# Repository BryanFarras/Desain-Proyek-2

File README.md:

# Autonomous Evacuation Rover (AER)

Autonomous Evacuation Rover (AER) is an integrated mobile robotics platform developed for autonomous exploration, mapping, hazard detection, and evacuation assistance in unknown or hazardous indoor environments. The system combines ROS 2-based autonomous navigation (SLAM and Nav2), real-time deep learning obstacle detection (YOLOv8), an embedded dual-motor controller (ESP32 and TB6612FNG), and a real-time web monitoring dashboard designed for both onboard touchscreen kiosks and remote operator telemetry.

---

## Table of Contents

- [System Architecture](#system-architecture)
- [Key Features](#key-features)
- [Repository Structure](#repository-structure)
- [Hardware Specifications](#hardware-specifications)
- [Software Stack and Prerequisites](#software-stack-and-prerequisites)
- [Installation and Environment Setup](#installation-and-environment-setup)
  - [Automated Installation](#automated-installation)
  - [Manual Installation](#manual-installation)
- [Subsystem Configuration and Execution](#subsystem-configuration-and-execution)
  - [1. Web Monitoring System](#1-web-monitoring-system)
  - [2. Computer Vision and Obstacle Detection](#2-computer-vision-and-obstacle-detection)
  - [3. ROS 2 Simulation, SLAM, and Navigation](#3-ros-2-simulation-slam-and-navigation)
  - [4. ESP32 Motor Controller Firmware](#4-esp32-motor-controller-firmware)
- [Communication and Control Protocols](#communication-and-control-protocols)
  - [ESP32 UART Serial Protocol](#esp32-uart-serial-protocol)
  - [Web Monitoring Endpoints](#web-monitoring-endpoints)
  - [ROS 2 Topic Architecture](#ros-2-topic-architecture)
- [Hardware Design and PCB](#hardware-design-and-pcb)
- [Troubleshooting](#troubleshooting)
- [License and Project Information](#license-and-project-information)

---

## System Architecture

The robot utilizes a distributed computing model comprising a primary Single Board Computer (Raspberry Pi 4B) and an auxiliary Microcontroller Unit (ESP32 DOIT DevKit V1), linked over high-speed USB-UART serial communication:

```
+-----------------------------------------------------------------------+
|                    Raspberry Pi 4B (Host Computer)                    |
|                                                                       |
|  +---------------------------+       +-----------------------------+  |
|  |     ROS 2 Jazzy Stack     |       |   Computer Vision Pipeline  |  |
|  |  - SLAM Toolbox (Mapping) |       |  - YOLOv8 Obstacle Model    |  |
|  |  - Beluga AMCL (Localize) |       |  - Picamera2 / OpenCV       |  |
|  |  - Nav2 (Path Planning)   |       |  - Real-time Bounding Boxes |  |
|  +-------------+-------------+       +--------------+--------------+  |
|                |                                    |                 |
|                +------------------+-----------------+                 |
|                                   |                                   |
|                      +------------v------------+                      |
|                      |  Flask Monitoring Server|                      |
|                      |  - Telemetry Dashboard  |                      |
|                      |  - Live MJPEG Stream    |                      |
|                      |  - Mission Mode Control |                      |
|                      |  - Emergency Stop / HITL|                      |
|                      +------------+------------+                      |
|                                   |                                   |
|                         [Serial Bridge: 115200]                       |
+-----------------------------------|-----------------------------------+
                                    | USB-UART
+-----------------------------------v-----------------------------------+
|                        ESP32 DOIT DevKit V1                           |
|                                                                       |
|  - PWM Motor Generation (20 kHz, 8-bit resolution)                    |
|  - Bidirectional Movement Logic (Differential Drive)                 |
|  - TB6612FNG Dual H-Bridge Driver Interface                          |
|  - Safety Watchdog and Standby Management                            |
+-----------------------------------+-----------------------------------+
                                    |
                            +-------v-------+
                            | DC Gear Motors|
                            +---------------+
```

---

## Key Features

- **Autonomous Navigation and SLAM**: Full ROS 2 navigation integration utilizing `slam_toolbox` for 2D LiDAR mapping, `beluga_amcl` for probabilistic particle-filter localization, and `nav2` for global/local path planning and dynamic costmaps.
- **Deep Learning Obstacle Detection**: Onboard real-time inference using YOLOv8 Nano models tailored for low-power edge compute, supporting Picamera2 on Raspberry Pi OS and OpenCV fallback on desktop workstations.
- **Dedicated Low-Level Motor Control**: ESP32 firmware running high-frequency 20 kHz PWM for quiet and responsive motor actuation, eliminating timing jitter and isolating motor power noise from the primary processor.
- **Comprehensive Web Monitoring Interface**: Flask-based web dashboard offering live teleoperation, real-time telemetry gauges (odometry, yaw, speed, battery, CPU/RAM stats), MJPEG video feed, dynamic whitelisted system diagnostics, and hardware emergency stop triggers.
- **Touchscreen Kiosk Capability**: Optimized layout for 3.2-inch to 7-inch Raspberry Pi LCDs with support for full-screen Chromium kiosk autostart and background systemd service operation.
- **Custom Hardware Infrastructure**: Dedicated custom PCB designs (Gerber files provided) for clean power delivery, level shifting, motor driver routing, and sensor connectivity.

---

## Repository Structure

```
.
|-- Computer Vision/              # AI training pipelines and camera inference
|   |-- cv_ws/                    # Computer vision workspace resources
|   |-- requirements.txt          # CV specific Python dependencies
|   |-- run_picam_rover.py        # Real-time YOLOv8 camera inference runner
|   |-- standalone_cv.py          # Standalone video test script
|   |-- train_rover.py            # Model training and export (ONNX, TFLite, NCNN)
|   `-- README_TRAINING_PICAM.md  # Detailed training and deployment documentation
|-- Dataset CV/                   # Training and validation datasets for obstacle detection
|-- Docs/                         # Project documentation and setup guides
|   `-- LANGKAH_PEMBUATAN_MODEL_CV.md # Indonesian guide for CV model creation
|-- Monitoring System/            # Legacy telemetry and monitoring code
|-- New Monitoring System/        # Production Flask monitoring and control dashboard
|   |-- aer-dashboard.service     # Systemd unit file for autostart
|   |-- camera_stream.py          # Multi-backend camera streamer (Picamera2/OpenCV)
|   |-- main.py                   # Primary Flask application server and state machine
|   |-- requirements.txt          # Dashboard Python dependencies
|   |-- ros2_node.py              # ROS 2 rclpy node bridge for telemetry
|   |-- serial_bridge.py          # UART communication driver for ESP32
|   |-- setup.sh                  # Dashboard quick-setup script
|   |-- static/                   # CSS stylesheets, JavaScript files, and assets
|   |-- templates/                # Jinja2 HTML dashboard templates
|   `-- README.md                 # Detailed dashboard documentation
|-- PCB/                          # Hardware design files and manufacturing archives
|   |-- Gerber New/               # Updated PCB Gerber fabrication files
|   `-- Rover Gerber/             # Primary chassis PCB Gerber package
|-- RoverESP/                     # ESP32 motor controller firmware (PlatformIO)
|   |-- include/                  # C++ header files
|   |-- lib/                      # PlatformIO modular libraries
|   |-- platformio.ini            # PlatformIO board and build configuration
|   `-- src/
|       |-- TB6612FNG.cpp         # TB6612FNG motor driver implementation
|       `-- main.cpp              # Serial listener and motor actuation loop
|-- Rover_Sim/                    # ROS 2 simulation and autonomy workspace
|   |-- maze_map_save.pgm         # Saved occupancy grid map
|   |-- maze_map_save.yaml        # Map metadata configuration
|   `-- src/
|       |-- AREbot_description/   # Robot URDF, Xacro, meshes, and launch files
|       |-- beluga/               # Beluga localization library
|       |-- beluga_amcl/          # Beluga AMCL 2D localization ROS 2 package
|       |-- beluga_ros/           # Beluga ROS 2 integration wrappers
|       `-- ldlidar_stl_ros2/     # LDLiDAR STL-27L driver package
|-- INSTALL_DEPENDENCIES.md       # Multi-platform dependency installation guide
|-- install_all_dependencies.ps1  # Windows PowerShell automated installer
|-- install_all_dependencies.sh   # Linux/Raspberry Pi automated installer
|-- install_ros_dependencies.sh   # Ubuntu 24.04 ROS 2 Jazzy automated installer
|-- requirements.txt              # Root unified Python dependencies
`-- setup_python_env.sh           # Virtual environment configuration script
```

---

## Hardware Specifications

| Component | Model / Specification | Purpose |
| :--- | :--- | :--- |
| Single Board Computer | Raspberry Pi 4 Model B (4GB / 8GB) | High-level compute: ROS 2, SLAM, CV, Web Server |
| Microcontroller | ESP32 DOIT DevKit V1 (30-pin) | Low-level motor control, PWM generation, safety brake |
| Motor Driver | Toshiba TB6612FNG Dual H-Bridge | Drives left and right DC drive motors |
| Drive Motors | DC Gear Motors with Encoders | Differential drive locomotive base |
| Range Sensor | 2D LiDAR (LDLiDAR STL-27L / LD19) | Environment 360-degree range scanning for SLAM |
| Vision Sensor | Raspberry Pi Camera Module 2/3 or USB Cam | Video stream capture and YOLOv8 object detection |
| Display | 3.2-inch to 7-inch LCD Display | Onboard dashboard for local telemetry and status |
| Power Supply | Li-Ion 3S / 2S Pack + Buck Regulators | Independent 5V logic and 7.4V-12V motor supply rails |
| Custom PCB | 2-layer FR4 Custom Board | Power distribution, MCU mounting, and header breakouts |

---

## Software Stack and Prerequisites

- **Operating System**: Ubuntu 24.04 LTS (Noble Numbat) recommended for ROS 2 Jazzy; Raspberry Pi OS 64-bit (Debian Bookworm) supported for the physical robot deployment.
- **Robotics Middleware**: ROS 2 Jazzy Jalisco (or ROS 2 Humble Hawksbill on Ubuntu 22.04).
- **Python Runtime**: Python 3.10 or higher.
- **Embedded Toolchain**: PlatformIO Core (`pio`) or PlatformIO IDE in VS Code.
- **Core Python Packages**:
  - `flask >= 3.0.0`
  - `psutil >= 5.9.0`
  - `pyserial >= 3.5`
  - `opencv-python >= 4.8.0`
  - `numpy >= 1.24.0`
  - `ultralytics >= 8.0.0`
  - `torch`, `torchvision`
  - `transforms3d >= 0.4.0`
  - `websockets >= 12.0`

---

## Installation and Environment Setup

### Automated Installation

#### Linux and Raspberry Pi OS (One-Line Execution)

For standard application dependencies (Flask, PySerial, OpenCV, YOLO, system libraries):

```bash
chmod +x install_all_dependencies.sh && ./install_all_dependencies.sh
```

For a complete ROS 2 Jazzy installation with Nav2, Gazebo, and simulation dependencies on Ubuntu 24.04 LTS:

```bash
sudo bash install_ros_dependencies.sh
```

#### Windows (PowerShell)

Open PowerShell as Administrator in the root repository directory:

```powershell
Set-ExecutionPolicy -Scope Process -ExecutionPolicy Bypass
.\install_all_dependencies.ps1
```

---

### Manual Installation

#### 1. System Packages (Linux)

```bash
sudo apt-get update && sudo apt-get install -y \
    python3 python3-pip python3-venv python3-dev \
    build-essential libgl1-mesa-glx libglib2.0-0 \
    libgstreamer1.0-0 v4l-utils
```

If deploying on Raspberry Pi with the official camera:

```bash
sudo apt-get install -y python3-picamera2
```

#### 2. Python Virtual Environment

Create a virtual environment with `--system-site-packages` so ROS 2 (`rclpy`) and `picamera2` system bindings remain accessible:

```bash
python3 -m venv --system-site-packages .venv
source .venv/bin/activate
pip install --upgrade pip
pip install -r requirements.txt
```

#### 3. Serial Port Permissions (Linux)

Grant your user access to USB serial devices (`/dev/ttyUSB0` or `/dev/ttyACM0`):

```bash
sudo usermod -aG dialout $USER
```

Log out and back in for this change to take effect.

---

## Subsystem Configuration and Execution

### 1. Web Monitoring System

The monitoring system runs a Flask server that bridges ROS 2 telemetry, camera video, and direct ESP32 serial communication.

```bash
# Activate environment
source .venv/bin/activate

# Launch the monitoring server
cd "New Monitoring System"
python main.py
```

The interface will be accessible in your browser at:
`http://localhost:5000` or `http://<ROBOT_IP>:5000`

#### Running as a Background System Service (Linux)

To enable the dashboard to start automatically on system boot:

```bash
sudo cp "New Monitoring System/aer-dashboard.service" /etc/systemd/system/
sudo systemctl daemon-reload
sudo systemctl enable aer-dashboard.service
sudo systemctl start aer-dashboard.service
```

#### Kiosk Mode Configuration (Raspberry Pi Display)

To launch the dashboard full-screen in Chromium on desktop login, create an autostart entry:

```bash
mkdir -p ~/.config/autostart
cat << 'EOF' > ~/.config/autostart/aer-dashboard.desktop
[Desktop Entry]
Type=Application
Name=AER Dashboard
Exec=chromium-browser --kiosk --app=http://localhost:5000 --start-fullscreen
EOF
```

---

### 2. Computer Vision and Obstacle Detection

#### Real-Time Camera Inference

Run the detection pipeline using either a connected Raspberry Pi Camera or standard USB/OpenCV webcam:

```bash
cd "Computer Vision"

# Using OpenCV / USB Webcam:
python run_picam_rover.py --cam opencv --cam-id 0

# Using Raspberry Pi Camera Module:
python run_picam_rover.py --cam picam --conf 0.45
```

#### Model Training and Export

To train a new YOLOv8 obstacle detection model on your custom dataset:

```bash
cd "Computer Vision"
python train_rover.py --epochs 50 --imgsz 416 --batch 16 --model yolov8n.pt
```

After training, the best model weights will be saved to `runs/rover_train/rover_obstacle_model/weights/best.pt` and automatically exported to ONNX and TFLite formats for optimized execution on low-power devices.

---

### 3. ROS 2 Simulation, SLAM, and Navigation

#### Building the Simulation Workspace

```bash
source /opt/ros/jazzy/setup.bash
cd Rover_Sim
colcon build --symlink-install
source install/setup.bash
```

#### Launching Gazebo Simulation

Launch the AREbot robot model within the Gazebo simulation environment:

```bash
ros2 launch AREbot_description gazebo.launch.py
```

#### Running 2D SLAM Mapping

In a separate terminal:

```bash
source Rover_Sim/install/setup.bash
ros2 launch AREbot_description online_async_launch.py
```

#### Running Beluga AMCL Localization

To localize the robot within a pre-mapped environment:

```bash
source Rover_Sim/install/setup.bash
ros2 launch AREbot_description beluga_localizaton_amcl.launch.py
```

#### Launching Nav2 Autonomous Navigation

```bash
source Rover_Sim/install/setup.bash
ros2 launch AREbot_description nav2_script.launch.py
```

---

### 4. ESP32 Motor Controller Firmware

The firmware in `RoverESP` handles motor actuation and receives direction commands from the Raspberry Pi over UART.

#### Building and Uploading with PlatformIO

1. Connect the ESP32 to your workstation via USB.
2. Navigate to the `RoverESP` directory:
   ```bash
   cd RoverESP
   ```
3. Compile the firmware:
   ```bash
   pio run
   ```
4. Upload the binary to the ESP32:
   ```bash
   pio run --target upload
   ```
5. Open the serial monitor to verify operation:
   ```bash
   pio device monitor --baud 115200
   ```

---

## Communication and Control Protocols

### ESP32 UART Serial Protocol

The ESP32 listens on UART (115200 baud, 8N1) for single-character ASCII control commands:

| Command Character | Action | Description |
| :---: | :--- | :--- |
| `w` | Forward | Both motors rotate forward at `currentSpeed` |
| `s` | Backward | Both motors rotate backward at `currentSpeed` |
| `a` | Turn Left | Steer left (Right motor forward, Left motor reduced) |
| `d` | Turn Right | Steer right (Left motor forward, Right motor reduced) |
| `q` | Spin Left | Counter-clockwise in-place rotation |
| `e` | Spin Right | Clockwise in-place rotation |
| ` ` (Space) | Coast Stop | Disables motor PWM, allowing free rolling |
| `b` | Short Brake | Actuates active brake on both H-bridges |
| `+` | Speed Increment | Increases default PWM speed by +20 (Max 255) |
| `-` | Speed Decrement | Decreases default PWM speed by -20 (Min 0) |
| `t` | Automated Demo | Runs pre-programmed motion self-test |
| `h` | Help Menu | Prints serial command help interface |

---

### Web Monitoring Endpoints

| Endpoint | HTTP Method | Function |
| :--- | :---: | :--- |
| `/` | GET | Serves the primary monitoring web dashboard |
| `/video_feed` | GET | Streams live MJPEG video with overlay graphics |
| `/status` | GET | Returns JSON payload of real-time telemetry, sensors, and status |
| `/exec_command` | POST | Executes pre-whitelisted system diagnostic commands safely |
| `/api/mode` | POST | Changes the operational mode (STANDBY, PATROL, EVACUATION, MANUAL) |
| `/api/control` | POST | Dispatches direct motor commands to the serial bridge |

---

### ROS 2 Topic Architecture

| Topic Name | Message Type | Description |
| :--- | :--- | :--- |
| `/cmd_vel` | `geometry_msgs/msg/Twist` | Velocity command input for differential drive |
| `/odom` | `nav_msgs/msg/Odometry` | Odometry state published by controllers |
| `/scan` | `sensor_msgs/msg/LaserScan` | 2D LiDAR range measurements |
| `/map` | `nav_msgs/msg/OccupancyGrid` | 2D SLAM generated grid map |
| `/amcl_pose` | `geometry_msgs/msg/PoseWithCovarianceStamped` | Estimated robot pose from localization |
| `/joint_states` | `sensor_msgs/msg/JointState` | Wheel joint angular position and velocity |

---

## Hardware Design and PCB

Custom circuit board designs for the Autonomous Evacuation Rover are stored in the `PCB` directory:

- **`PCB/Gerber New/`**: Latest production-ready Gerber archives including drill files, solder masks, copper traces, and silkscreen layers.
- **`PCB/Rover Gerber/`**: Baseline chassis interface board supporting ESP32 socket mounting, TB6612FNG daughterboard pinouts, logic-level regulation, and direct screw-terminal motor connections.

To manufacture these boards, submit the respective Gerber directory as a ZIP archive to standard PCB fabrication services.

---

## Troubleshooting

### Serial Port Access Issues on Linux
If the web monitoring system reports serial connection failure:
1. Verify device enumeration: `ls -l /dev/ttyUSB* /dev/ttyACM*`
2. Add your user account to the serial group: `sudo usermod -aG dialout $USER`
3. Reload permissions or reboot the system.

### Missing OpenGL / Display Libraries (`libGL.so.1`)
When running OpenCV on headless Linux systems or minimal server installations:
```bash
sudo apt-get install -y libgl1-mesa-glx libglib2.0-0
```

### Camera Device Busy or Not Found
1. Ensure the camera ribbon cable is firmly seated and enabled in `raspi-config` (Interface Options -> Camera).
2. Check available video capture nodes: `v4l2-ctl --list-devices`
3. Test using the standalone utility: `python "Computer Vision/standalone_cv.py"`

### ROS 2 Environment Not Sourced
If ROS commands or packages are not recognized:
```bash
source /opt/ros/jazzy/setup.bash
source Rover_Sim/install/setup.bash
```
Ensure these lines are added to your `~/.bashrc` file for automatic sourcing in new terminal sessions.

---

## License and Project Information

This project is developed as part of **Desain Proyek 2 (Despro)**.
Repository: [BryanFarras/Desain-Proyek-2](https://github.com/BryanFarras/Desain-Proyek-2)

All code and design documentation are maintained for educational and research purposes in autonomous mobile robotics and disaster response applications.

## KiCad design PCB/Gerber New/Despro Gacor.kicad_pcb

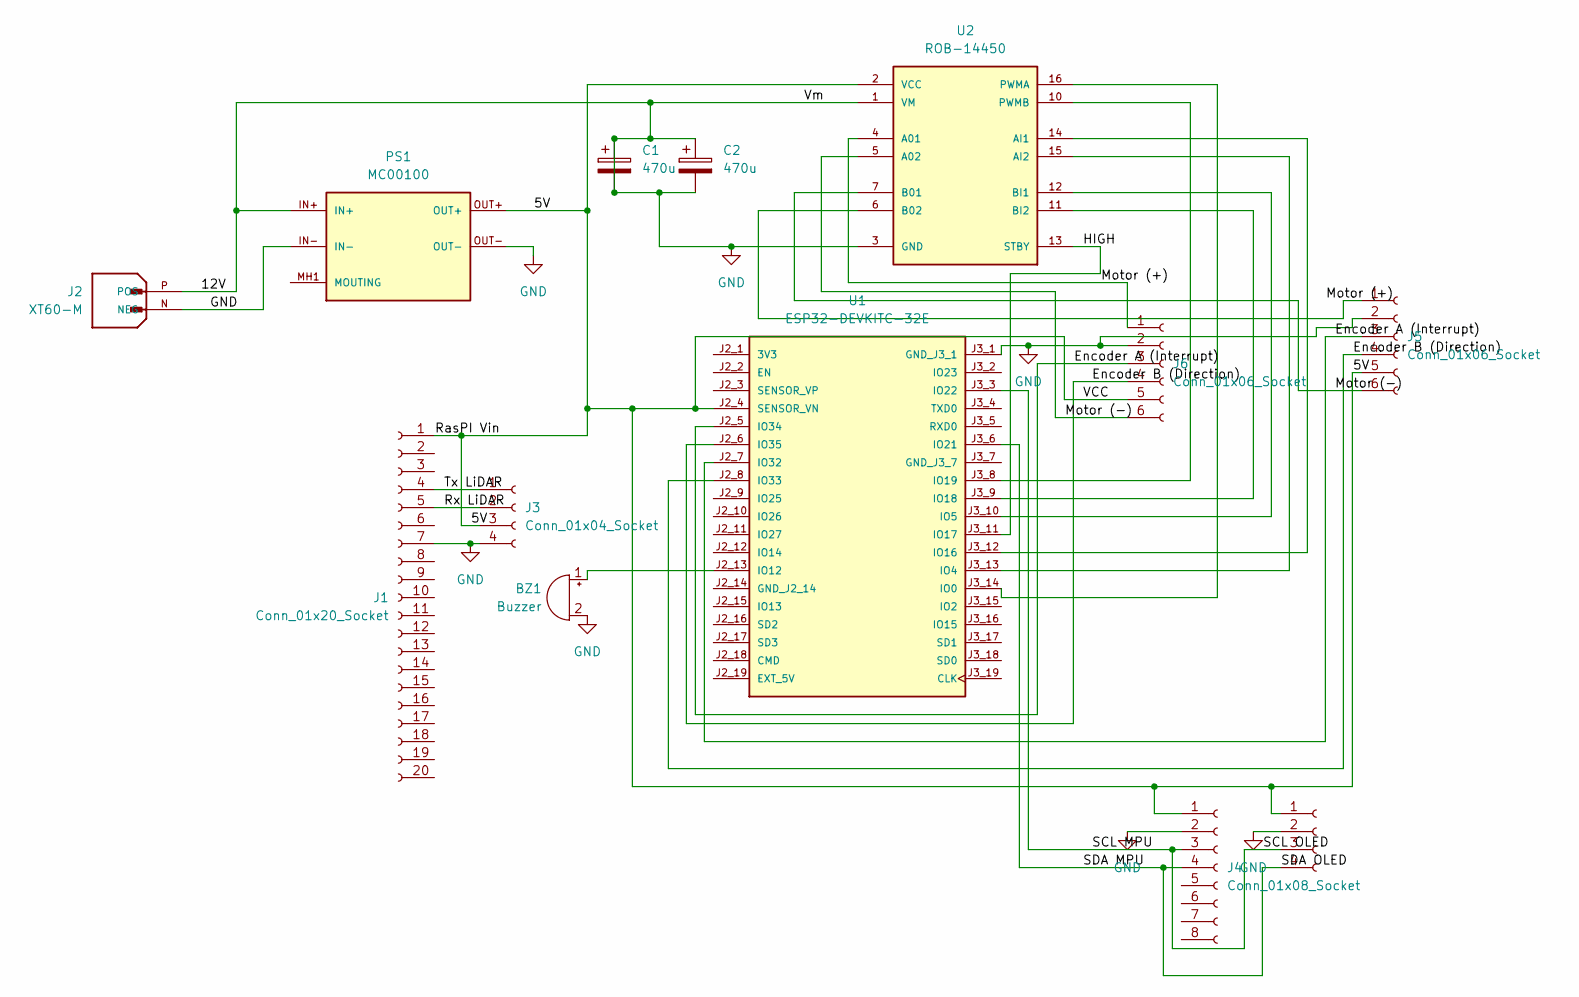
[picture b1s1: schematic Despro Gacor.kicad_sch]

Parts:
BZ1: Buzzer; Buzzer_12x9.5RM7.6
C1, C2: 470u; CP_Radial_D10.0mm_P5.00mm
J1: Conn_01x20_Socket; PinSocket_1x20_P2.54mm_Vertical
J2: XT60-M; AMASS_XT60-M; PARTREV V1.2
J3, J9: Conn_01x04_Socket; PinSocket_1x04_P2.54mm_Vertical
J4: Conn_01x08_Socket; PinSocket_1x08_P2.54mm_Vertical
J5, J6: Conn_01x06_Socket; PinSocket_1x06_P2.54mm_Vertical
PS1: MC00100; CONV_MC00100; PARTREV NA
U1: ESP32-DEVKITC-32E; MODULE_ESP32-DEVKITC-32E; PARTREV 1.4
U2: ROB-14450; MODULE_ROB-14450; PARTREV 11-13-17

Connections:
/5V: J1.1, J3.3, J4.1, J5.5, J6.5, J9.1, PS1.OUT+, U1.J2_4 (SENSOR_VN), U2.2 (VCC)
/Encoder B (Direction): J5.4, J6.4, U1.J2_6 (IO35), U1.J2_8 (IO33)
/HIGH: U1.J3_11 (IO17), U2.13 (STBY)
/Motor (+): J6.1, U2.4 (A01)
/Motor (-): J5.6, J6.6, U2.5 (A02), U2.7 (B01)
/Rx LiDAR: J1.5, J3.2
/SCL MPU: J4.3, J9.3, U1.J3_3 (IO22)
/SDA MPU: J4.4, J9.4, U1.J3_6 (IO21)
/Tx LiDAR: J1.4, J3.1
unnamed: BZ1.1 (+), U1.J2_13 (IO12)
unnamed: J5.1, U2.6 (B02)
unnamed: PS1.MH1 (MOUTING), PS1.MH2 (MOUTING)
unnamed: U1.J3_14 (IO0), U2.16 (PWMA)
unnamed: U1.J3_13 (IO4), U2.15 (AI2)
unnamed: U1.J3_10 (IO5), U2.12 (BI1)
unnamed: U1.J3_12 (IO16), U2.14 (AI1)
unnamed: U1.J3_9 (IO18), U2.11 (BI2)
unnamed: U1.J3_8 (IO19), U2.10 (PWMB)

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
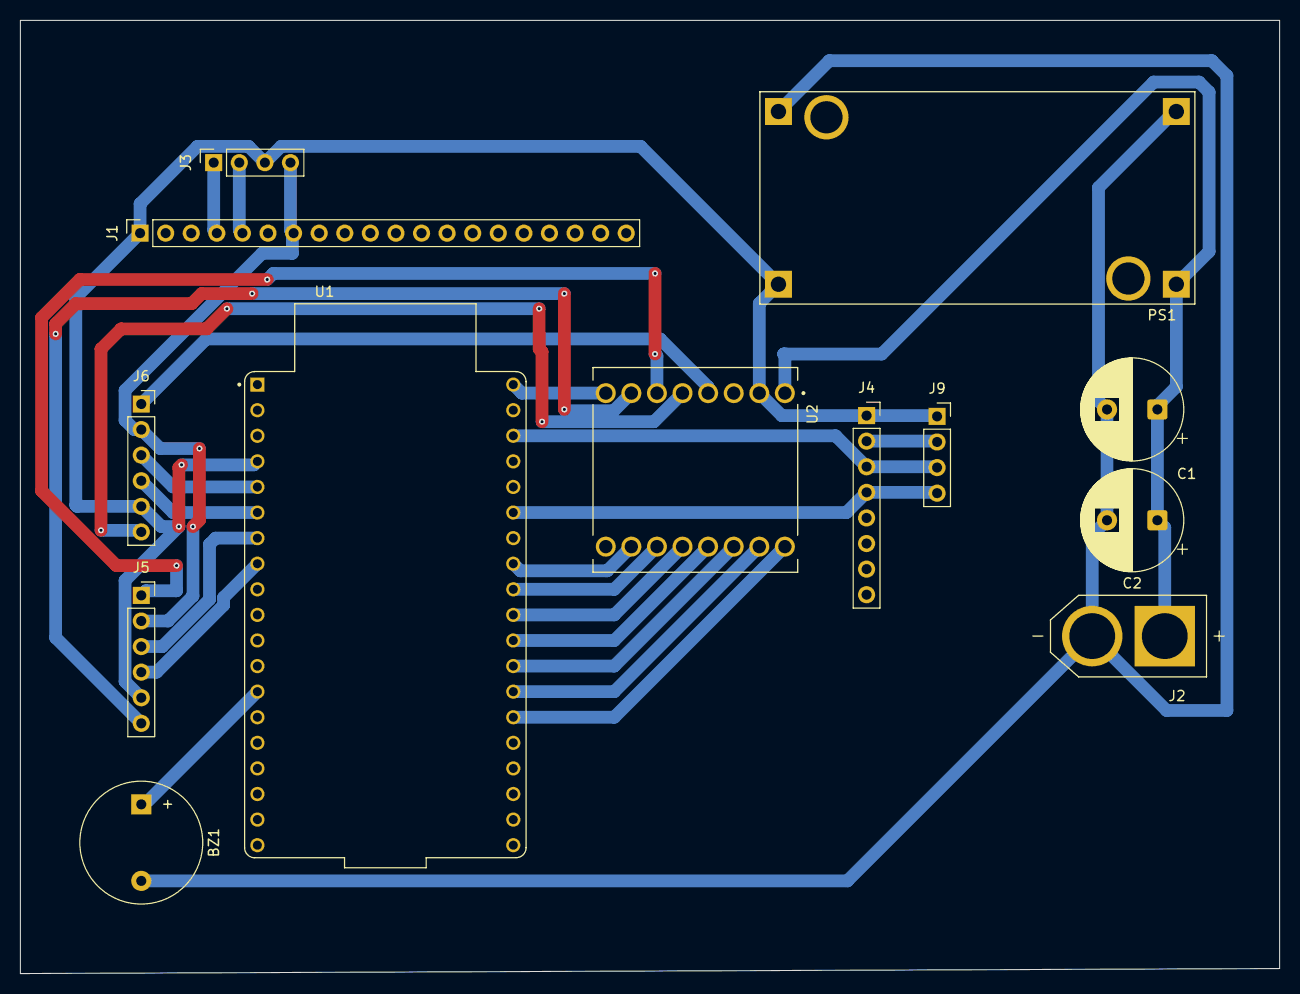
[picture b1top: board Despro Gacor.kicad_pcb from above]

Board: 4 copper layers, 125.0 x 94.6 mm, 13 parts (0 on the bottom side), 21 nets.
